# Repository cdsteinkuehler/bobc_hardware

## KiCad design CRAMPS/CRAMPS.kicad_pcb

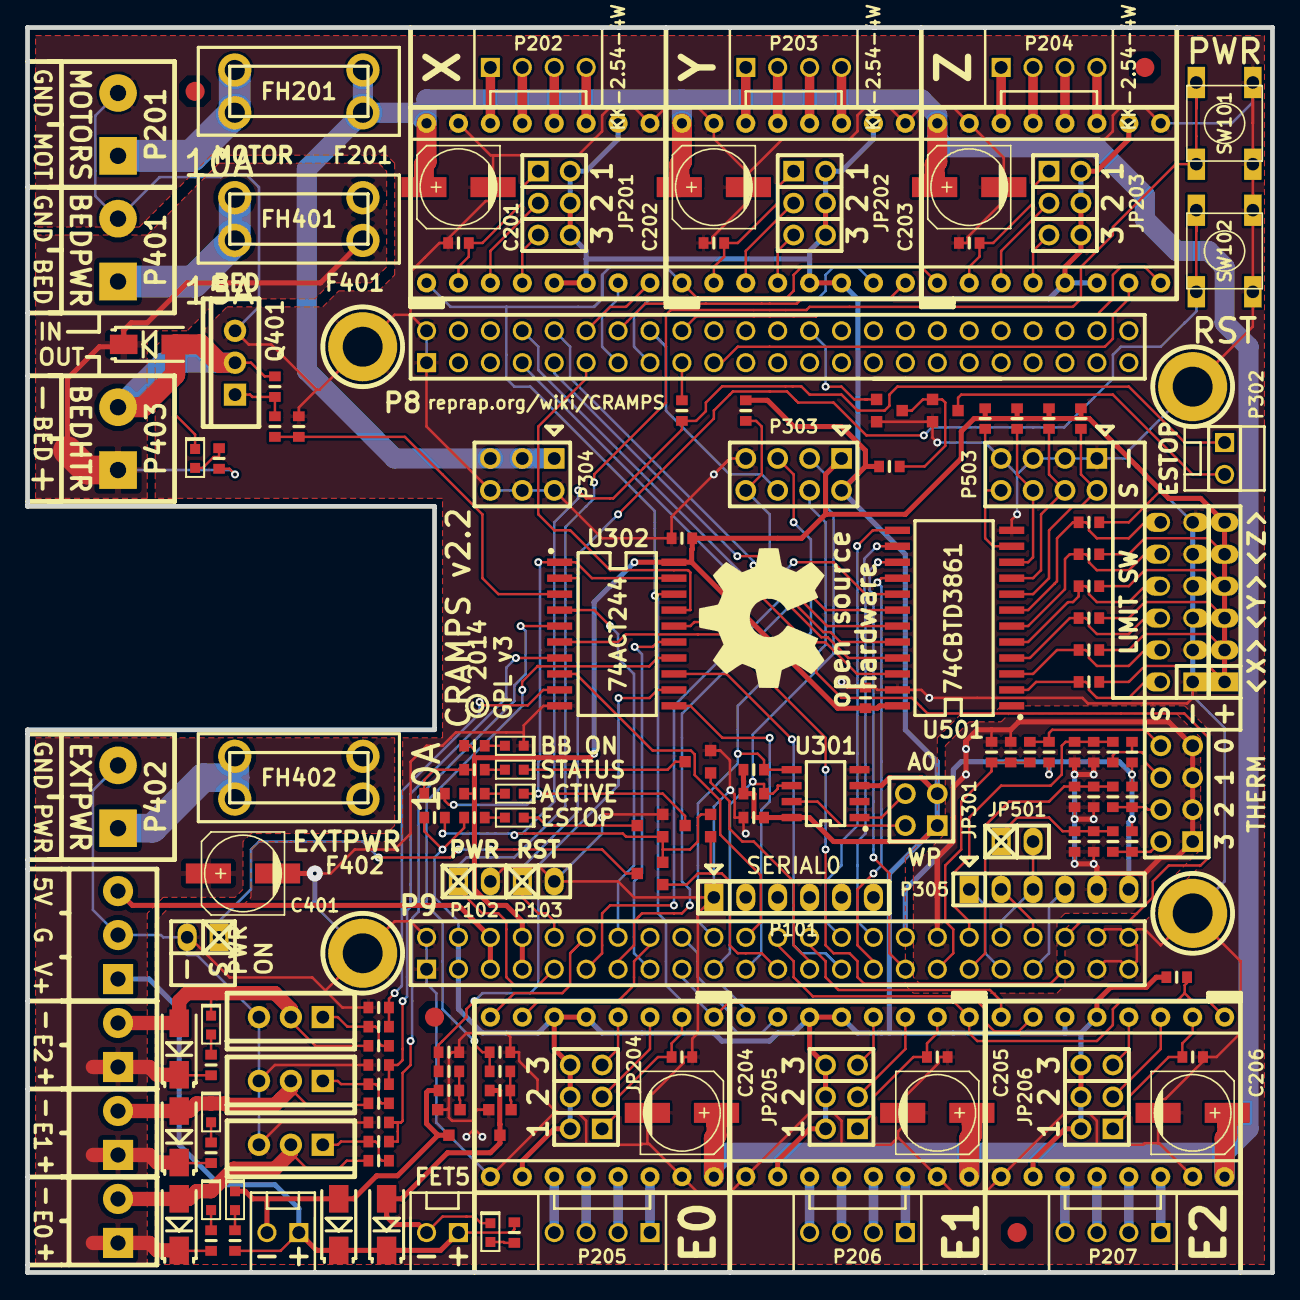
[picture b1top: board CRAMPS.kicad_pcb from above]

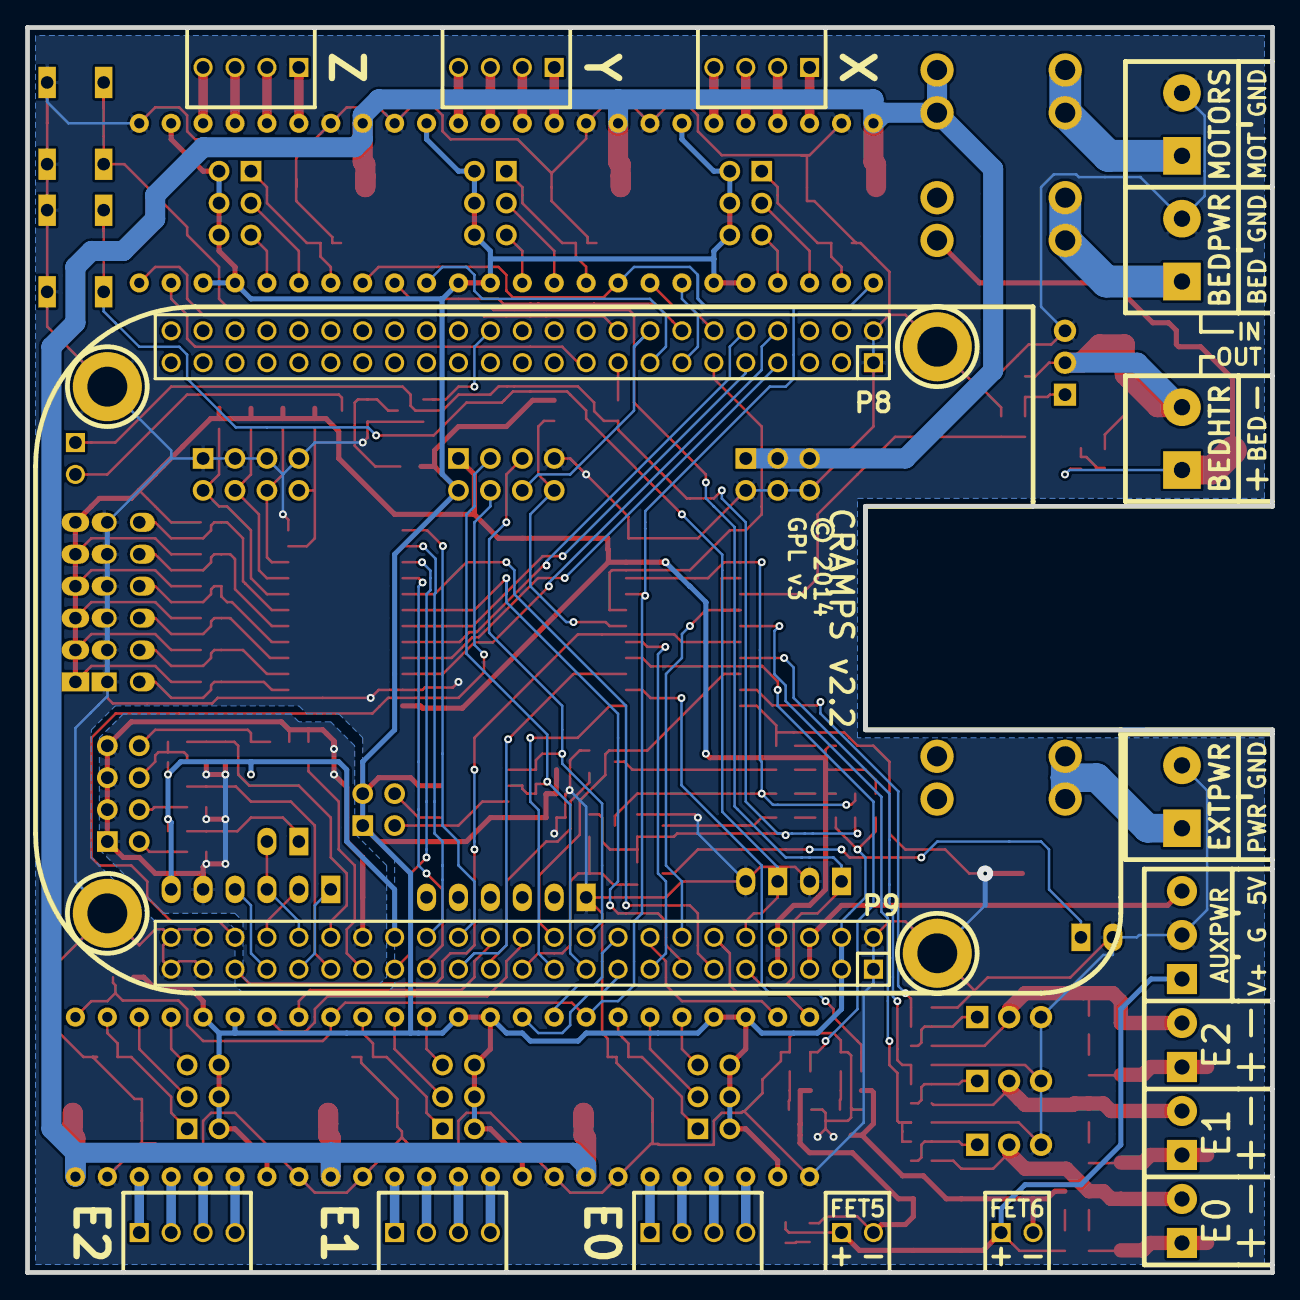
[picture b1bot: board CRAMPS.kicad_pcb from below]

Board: 2 copper layers, 99.1 x 99.1 mm, 192 parts (3 on the bottom side), 155 nets.

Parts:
BB101: BeagleBone Black; BeagleBone-Pins
C201, C202, C203, C204, C205, C206, C401: 100u 35V; c_elec_6.3x7.7
C301, C302, C501, C502, C503, C504, C505: 100n; CAPC1608x55N
C402, C403, C404, C405, C406, C407: None; CAPC1608x55N
C506, C507, C508, C509: 10u; CAPC1608x55N
D401, D402, D403, D404, D405, D406: SS14; DIOM5127X229N
F201, F402: 10A; Fuse-Loose
F401: 15A; Fuse-Loose
FH201, FH401, FH402: FUSE-HOLDER; Keystone-3568
FID1, FID2, FID3, FID4: VAL**; FIDUCIAL-060
JP201, JP202, JP203, JP204, JP205, JP206: HEADER_3X2; pin_strip_3x2
JP301: HEADER_2X2; pin_strip_2x2
JP501: HEADER_2; pin_strip_2
LD101, LD401, LD402, LD403, LD404, LD405, LD406: Yellow; OSRAM-LED-0603
LD102, LD301: Green; OSRAM-LED-0603
LD302: Red; OSRAM-LED-0603
M101: PCB_GREEN_RMC; OSHW_logo_2
M102: LOGO_OSHW; PCB_GREEN_RMC
P8, P9: BB_EXP_CONN; P8P9_PinHeader
P101: SOCKET_6_LONG; pin_strip_6
P102, P103, P301: HEADER_2; pin_strip_2
P201, P401, P402, P403: VAL**; PT_2,5-2-5,0-H
P202, P203, P204, P205, P206, P207: KK-2.54-4W; CONN_KK_2.54_4W
P208, P209, P210, P211: POLOLU_SOCKET; Pololu_Socket
P302, P407, P409: KK-2.54-2W; CONN_KK_2.54_2W
P303, P503, P504: HEADER_4X2; pin_strip_4x2
P304: HEADER_3X2; pin_strip_3x2
P305, P501: HEADER_6; pin_strip_6
P404: VAL**; PT_1,5-3-3,5-H
P405, P406, P408: VAL**; PT_1,5-2-3,5-H
P502: HEADER_6X2; pin_strip_6x2
Q101, Q301, Q302, Q303, Q304, Q305: 2N7002K; SOT23GDS
Q401, Q402, Q403, Q405: IRLB8743PBF; TO-220AB_IRF2804_RMC
Q404, Q406: DMN2075U; SOT23GDS
R101, R102, R303: 330R; RESC1608x55N
R201, R202, R203, R204, R205, R206: 100k; RESC1608x55N
R301, R308, R309, R310, R311, R312, R313, R315, R316, R501, R502, R503, R504, R505, R506, R507, R508, R509, R510: 10k; RESC1608x55N
R302, R402, R404, R406, R408, R410, R412: 2K7; RESC1608x55N
R304, R306, R307, R314, R515, R516, R517, R518: 4k7; RESC1608x55N
R305, R401, R403, R405, R407, R409, R411: 220R; RESC1608x55N
R511, R512, R513, R514: 2K0 1%; RESC1608x55N
S201, S202, S203, S204, S205, S206, S207, S208, S209, S210, S211, S212, S213, S214, S215, S216, S217, S218, S301, S501: SHUNT; Shunt
SW101, SW102: SW_PUSH; SW_6x6_MULTI
U201, U202, U203, U204, U205, U206: Pololu; POLOLU
U301: 24C256; SOIC127P600X175-8AN
U302: 74ACT244; SOIC127P1032X265-20N
U501: 74CBTD3861; SOIC127P1030X265-24N

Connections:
+V_MOTOR: C201.1, C202.1, C203.1, C204.1, C205.1, C206.1, FH201.3, FH201.4, P304.1, P304.3, P304.5, U201.16, U202.16, U203.16, U204.16, U205.16, U206.16
/Emergency Stop/MACHINE_PWRn: LD301.K, Q304.D, R308.2, U302.1, U302.19
/Emergency Stop/PS-On: P301.1, Q302.D
/Inputs/MISO-5V: P503.2, R507.2, U501.8
/Inputs/MOSI-5V: P503.6, R509.2, U501.10
/Inputs/SCK-5V: P503.4, R508.2, U501.9
/Inputs/SPI_CS0-5V: P503.8, R510.2, U501.11
/Mosfet Outputs/Aux_Pwr: D404.K, D406.K, P404.1, P407.1, P409.1, R408.1, R412.1
/Mosfet Outputs/Bed_Fused: D401.K, FH401.3, FH401.4, P403.1, R402.1
/Mosfet Outputs/Bed_HTR: C402.1, D401.A, LD401.K, P403.2, Q401.D
/Mosfet Outputs/Bed_Pwr: FH401.1, FH401.2, P401.1
/Mosfet Outputs/E0_HTR: C403.1, D402.A, LD402.K, P405.2, Q402.D
/Mosfet Outputs/E1_HTR: C404.1, D403.A, LD403.K, P406.2, Q403.D
/Mosfet Outputs/E2_HTR: C405.1, D405.A, LD405.K, P408.2, Q405.D
/Mosfet Outputs/Ext_Fused: C401.1, D402.K, D403.K, D405.K, FH402.3, FH402.4, P405.1, P406.1, P408.1, R404.1, R406.1, R410.1
/Mosfet Outputs/Ext_Pwr: FH402.1, FH402.2
/Mosfet Outputs/P_FET5: C406.1, D404.A, LD404.K, P407.2, Q404.D
/Mosfet Outputs/P_FET6: C407.1, D406.A, LD406.K, P409.2, Q406.D
/Stepper Drivers/E01A: P205.3, U204.12
/Stepper Drivers/E01B: P205.4, U204.11
/Stepper Drivers/E02A: P205.2, U204.13
/Stepper Drivers/E02B: P205.1, U204.14
/Stepper Drivers/E11A: P206.3, U205.12
/Stepper Drivers/E11B: P206.4, U205.11
/Stepper Drivers/E12A: P206.2, U205.13
/Stepper Drivers/E12B: P206.1, U205.14
/Stepper Drivers/E21A: P207.3, U206.12
/Stepper Drivers/E21B: P207.4, U206.11
/Stepper Drivers/E22A: P207.2, U206.13
/Stepper Drivers/E22B: P207.1, U206.14
/Stepper Drivers/MOT_IN: FH201.1, FH201.2, P201.1
/Stepper Drivers/X1A: P202.3, U201.12
/Stepper Drivers/X1B: P202.4, U201.11
/Stepper Drivers/X2A: P202.2, U201.13
/Stepper Drivers/X2B: P202.1, U201.14
/Stepper Drivers/Y1A: P203.3, U202.12
/Stepper Drivers/Y1B: P203.4, U202.11
/Stepper Drivers/Y2A: P203.2, U202.13
/Stepper Drivers/Y2B: P203.1, U202.14
/Stepper Drivers/Z1A: P204.3, U203.12
/Stepper Drivers/Z1B: P204.4, U203.11
/Stepper Drivers/Z2A: P204.2, U203.13
/Stepper Drivers/Z2B: P204.1, U203.14
ADC_GND: C502.2, C503.2, C504.2, C505.2, C506.2, C507.2, C508.2, C509.2, P9.34, P305.5, P504.1, P504.3, P504.5, P504.7
ADC_VDD: P9.32, P305.6, R511.1, R512.1, R513.1, R514.1
AIN0: P9.39, P305.4
AIN1: P9.40, P305.2
AIN2: P9.37, P305.1
AIN3: JP501.2, P9.38, P305.3
AXIS_ENAn: P9.14, U302.2, U302.4
D3.3V: C301.1, JP201.2, JP201.4, JP201.6, JP202.2, JP202.4, JP202.6, JP203.2, JP203.4, JP203.6, JP204.2, JP204.4, JP204.6, JP205.2, JP205.4, JP205.6, JP206.2, JP206.4, JP206.6, JP301.1, JP301.3, P9.3, P9.4, P303.2, R301.1, R304.1, R305.1, R306.1, R307.1, R310.1, R314.1, U201.5, U201.6, U201.10, U202.5, U202.6, U202.10, U203.5, U203.6, U203.10, U204.5, U204.6, U204.10, U205.5, U205.6, U205.10, U206.5, U206.6, U206.10, U301.3, U301.8
DGND: BB101.M1, BB101.M2, BB101.M3, BB101.M4, C201.2, C202.2, C203.2, C204.2, C205.2, C206.2, C301.2, C302.2, C401.2, C501.2, LD102.K, P8.1, P8.2, P9.1, P9.2, P9.43, P9.44, P9.45, P9.46, P101.1, P102.2, P103.2, P201.2, P301.2, P303.7, P304.2, P304.4, P304.6, P401.2, P404.2, P502.1, P502.3, P502.5, P502.7, P502.9, P502.11, P503.1, P503.3, P503.5, P503.7, Q101.S, Q301.S, Q303.S, Q305.S, Q401.S, Q402.S, Q403.S, Q404.S, Q405.S, Q406.S, R201.2, R202.2, R203.2, R204.2, R205.2, R206.2, R309.2, R311.2, R312.2, R313.2, R315.2, R316.2, SW101.2, SW102.2, U201.9, U201.15, U202.9, U202.15, U203.9, U203.15, U204.9, U204.15, U205.9, U205.15, U206.9, U206.15, U301.4, U302.10, U501.12, U501.23
E0_DIR: P9.12, U204.8
E0_EN_BUFn: R314.2, U201.1, U202.1, U203.1, U204.1, U205.1, U206.1, U302.18
E0_STEP: P9.16, U204.7
E1_DIR: P9.18, U205.8
E1_STEP: P9.17, U205.7
E2_DIR: P9.26, U206.8
E2_STEP: P9.24, U206.7
EN_CRAMP3n: P303.8, R310.2, U302.16
ESTOP: P8.17, R302.2
ESTOP_SW: P8.26, Q301.G
FET1: P8.11, U302.17
FET1_BUF: R309.1, R401.2, U302.3
FET2: P9.15, U302.15
FET2_BUF: R311.1, R403.2, U302.5
FET3: P9.27, U302.13
FET3_BUF: R312.1, R405.2, U302.7
FET4: P9.21, U302.11
FET4_BUF: R313.1, R409.2, U302.9
FET5: P9.41, U302.6
FET5_BUF: R316.1, R407.2, U302.14
FET6: P9.22, U302.8
FET6_BUF: R315.1, R411.2, U302.12
LED: P9.25, Q101.G
MACHINE_PWR: P9.23, Q302.G, Q304.G
MISO: P9.29, U501.16
MOSI: P9.30, U501.14
unnamed: C402.2, Q401.G, R401.1
unnamed: C403.2, Q402.G, R403.1
unnamed: C404.2, Q403.G, R405.1
unnamed: C405.2, Q405.G, R409.1
unnamed: C406.2, Q404.G, R407.1
unnamed: C407.2, Q406.G, R411.1
unnamed: JP201.1, R201.1, U201.2
unnamed: JP201.3, U201.3
unnamed: JP201.5, U201.4
unnamed: JP202.1, R202.1, U202.2
unnamed: JP202.3, U202.3
unnamed: JP202.5, U202.4
unnamed: JP203.1, R203.1, U203.2
unnamed: JP203.3, U203.3
unnamed: JP203.5, U203.4
unnamed: JP204.1, R204.1, U204.2
unnamed: JP204.3, U204.3
unnamed: JP204.5, U204.4
unnamed: JP205.1, R205.1, U205.2
unnamed: JP205.3, U205.3
unnamed: JP205.5, U205.4
unnamed: JP206.1, R206.1, U206.2
unnamed: JP206.3, U206.3
unnamed: JP206.5, U206.4
unnamed: JP301.2, U301.7
unnamed: JP301.4, U301.1
unnamed: LD101.A, R101.2
unnamed: LD101.K, Q101.D
unnamed: LD102.A, R102.2
unnamed: LD301.A, R303.2
unnamed: LD302.A, R305.2
unnamed: LD302.K, Q305.D
unnamed: LD401.A, R402.2
unnamed: LD402.A, R404.2
unnamed: LD403.A, R406.2
unnamed: LD404.A, R408.2
unnamed: LD405.A, R410.2
unnamed: LD406.A, R412.2
unnamed: P302.1, Q302.S, Q304.S, Q305.G, R302.1, R304.2
unnamed: P302.2, Q303.D
unnamed: P502.2, R501.2, U501.2
unnamed: P502.4, R502.2, U501.3
unnamed: P502.6, R503.2, U501.4
unnamed: P502.8, R504.2, U501.5
unnamed: P502.10, R505.2, U501.6
unnamed: P502.12, R506.2, U501.7
unnamed: P504.2, R514.2, R518.2
unnamed: P504.4, R513.2, R517.2
unnamed: P504.6, R512.2, R516.2
unnamed: P504.8, R511.2, R515.2
unnamed: Q301.D, Q303.G, R301.2
PWR_BUT: P9.9, P102.1, SW101.1
RESETn: P9.10, P103.1, SW102.1
SCK: P9.31, U501.15
SCL: P9.19, P303.3, R306.2, U301.6
SDA: P9.20, P303.5, R307.2, U301.5
SPI_CS0: P9.28, U501.13
SPI_CS1: P9.42, P303.4
SPI_SPARE: P8.16, P303.6
SYS_5V: C302.1, C501.1, P9.7, P9.8, P303.1, P501.1, P501.2, P501.3, P501.4, P501.5, P501.6, R101.1, R102.1, R303.1, R308.1, R501.1, R502.1, R503.1, R504.1, R505.1, R506.1, R507.1, R508.1, R509.1, R510.1, U302.20, U501.24
THERM0: C502.1, C506.1, P9.33, R515.1
THERM1: C503.1, C507.1, P9.36, R516.1
THERM2: C504.1, C508.1, P9.35, R517.1
THERM3: C505.1, C509.1, JP501.1, R518.1
VDD_5V: P9.5, P9.6, P404.3
X-MAX: P8.7, U501.21
X-MIN: P8.8, U501.22
X_DIR: P8.12, U201.8
X_STEP: P8.13, U201.7
Y-MAX: P8.9, U501.19
Y-MIN: P8.10, U501.20
Y_DIR: P8.14, U202.8
Y_STEP: P8.15, U202.7
Z-MAX: P9.11, U501.17
Z-MIN: P9.13, U501.18
Z_DIR: P8.18, U203.8
Z_STEP: P8.19, U203.7

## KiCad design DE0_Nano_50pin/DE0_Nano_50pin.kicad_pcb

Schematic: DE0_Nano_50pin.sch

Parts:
C1, C2, C3, C4, C7, C8: 100n; CAPC1608x55N; PartNo GRM188R71C104KA01D
GPIO0, GPIO1: CONN_20X2; Pin_Socket_20x2; PartNo SFH11-PBPC-D20-ST-BK
LED1, LED2: Yellow; OSRAM-LED-0805; PartNo LY R976-PS-36
M1, M2, M3, M4: 4-40; MTH_4-40; PartNo Part of PCB
P2, P3, P4: CONN_25X2; pin_strip_25x2; PartNo 30350-6002HB
PTC1, PTC2: 2A; BOURNS-MF-NSMF; PartNo MF-NSMF200-2
R1, R2, R3, R4, R5, R6, R7, R8, R9, R10, R11, R12, R13, R14, R15, R16, R17, R18, R19, R20, R21, R22, R23, R24, R25, R26, R27, R28, R29, R30, R31, R32, R33, R34, R35, R36, R37, R38, R39, R40, R41, R42, R43, R44, R45, R46, R47, R48, R49, R50, R51, R52, R53, R54, R55, R56, R57, R58, R59, R60, R61, R62, R63, R64, R65, R66, R67, R68, R69, R70, R71, R72: 4.7k; RESC1608x55N; PartNo RMCF0603JT4K70
R98, R99: 240R; RESC1608x55N; PartNo RMCF0603JT240R
S1, S2, S3: SHUNT; Shunt; PartNo 382811-8
U1, U2, U3: 74CBT16211; SOP63P1035X279-56N; PartNo SN74CBTD16211ADGGR
W1, W2, W3: HEADER_3; pin_strip_3; PartNo M20-9990345

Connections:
+3.3V: GPIO0.29, GPIO1.29, R98.1, R99.1, W3.3
+5V: C7.1, C8.1, GPIO0.11, GPIO1.11, PTC1.2, PTC2.2, W3.1
/J1-PWR: PTC1.1, W1.1
/J2-PWR: PTC2.1, W2.1
/XIO0: P2.1, R1.2
/XIO1: P2.3, R2.2
/XIO2: P2.5, R3.2
/XIO3: P2.7, R4.2
/XIO4: P2.9, R5.2
/XIO5: P2.11, R6.2
/XIO6: P2.13, R7.2
/XIO7: P2.15, R8.2
/XIO8: P2.17, R9.2
/XIO9: P2.19, R10.2
/XIO10: P2.21, R11.2
/XIO11: P2.23, R12.2
/XIO12: P2.25, R13.2
/XIO13: P2.27, R14.2
/XIO14: P2.29, R15.2
/XIO15: P2.31, R16.2
/XIO16: P2.33, R17.2
/XIO17: P2.35, R18.2
/XIO18: P2.37, R19.2
/XIO19: P2.39, R20.2
/XIO20: P2.41, R21.2
/XIO21: P2.43, R22.2
/XIO22: P2.45, R23.2
/XIO23: P2.47, R24.2
/XIO24: P3.1, R25.2
/XIO25: P3.3, R26.2
/XIO26: P3.5, R27.2
/XIO27: P3.7, R28.2
/XIO28: P3.9, R29.2
/XIO29: P3.11, R30.2
/XIO30: P3.13, R31.2
/XIO31: P3.15, R32.2
/XIO32: P3.17, R33.2
/XIO33: P3.19, R34.2
/XIO34: P3.21, R35.2
/XIO35: P3.23, R36.2
/XIO36: P3.25, R37.2
/XIO37: P3.27, R38.2
/XIO38: P3.29, R39.2
/XIO39: P3.31, R40.2
/XIO40: P3.33, R41.2
/XIO41: P3.35, R42.2
/XIO42: P3.37, R43.2
/XIO43: P3.39, R44.2
/XIO44: P3.41, R45.2
/XIO45: P3.43, R46.2
/XIO46: P3.45, R47.2
/XIO47: P3.47, R48.2
/XIO48: P4.1, R49.2
/XIO49: P4.3, R50.2
/XIO50: P4.5, R51.2
/XIO51: P4.7, R52.2
/XIO52: P4.9, R53.2
/XIO53: P4.11, R54.2
/XIO54: P4.13, R55.2
/XIO55: P4.15, R56.2
/XIO56: P4.17, R57.2
/XIO57: P4.19, R58.2
/XIO58: P4.21, R59.2
/XIO59: P4.23, R60.2
/XIO60: P4.25, R61.2
/XIO61: P4.27, R62.2
/XIO62: P4.29, R63.2
/XIO63: P4.31, R64.2
/XIO64: P4.33, R65.2
/XIO65: P4.35, R66.2
/XIO66: P4.37, R67.2
/XIO67: P4.39, R68.2
/XIO68: P4.41, R69.2
/XIO69: P4.43, R70.2
/XIO70: P4.45, R71.2
/XIO71: P4.47, R72.2
GND: C3.2, C4.2, C7.2, C8.2, GPIO0.12, GPIO0.30, GPIO1.12, GPIO1.30, M1.1, M2.1, M3.1, M4.1, P2.2, P2.4, P2.6, P2.8, P2.10, P2.12, P2.14, P2.16, P2.18, P2.20, P2.22, P2.24, P2.26, P2.28, P2.30, P2.32, P2.34, P2.36, P2.38, P2.40, P2.42, P2.44, P2.46, P2.48, P2.50, P3.2, P3.4, P3.6, P3.8, P3.10, P3.12, P3.14, P3.16, P3.18, P3.20, P3.22, P3.24, P3.26, P3.28, P3.30, P3.32, P3.34, P3.36, P3.38, P3.40, P3.42, P3.44, P3.46, P3.48, P3.50, P4.2, P4.4, P4.6, P4.8, P4.10, P4.12, P4.14, P4.16, P4.18, P4.20, P4.22, P4.24, P4.26, P4.28, P4.30, P4.32, P4.34, P4.36, P4.38, P4.40, P4.42, P4.44, P4.46, P4.48, P4.50, W2.3; also elsewhere on the board
unnamed: P4.49, R49.1, R50.1, R51.1, R52.1, R53.1, R54.1, R55.1, R56.1, R57.1, R58.1, R59.1, R60.1, R61.1, R62.1, R63.1, R64.1, R65.1, R66.1, R67.1, R68.1, R69.1, R70.1, R71.1, R72.1
unnamed: LED2.A, R99.2
unnamed: LED1.A, R98.2
unnamed: P2.49, R1.1, R2.1, R3.1, R4.1, R5.1, R6.1, R7.1, R8.1, R9.1, R10.1, R11.1, R12.1, R13.1, R14.1, R15.1, R16.1, R17.1, R18.1, R19.1, R20.1, R21.1, R22.1, R23.1, R24.1
unnamed: C3.1, C4.1, W2.2
unnamed: C1.2, C2.2, W1.3
unnamed: C1.1, C2.1, W1.2
unnamed: P3.49, R25.1, R26.1, R27.1, R28.1, R29.1, R30.1, R31.1, R32.1, R33.1, R34.1, R35.1, R36.1, R37.1, R38.1, R39.1, R40.1, R41.1, R42.1, R43.1, R44.1, R45.1, R46.1, R47.1, R48.1

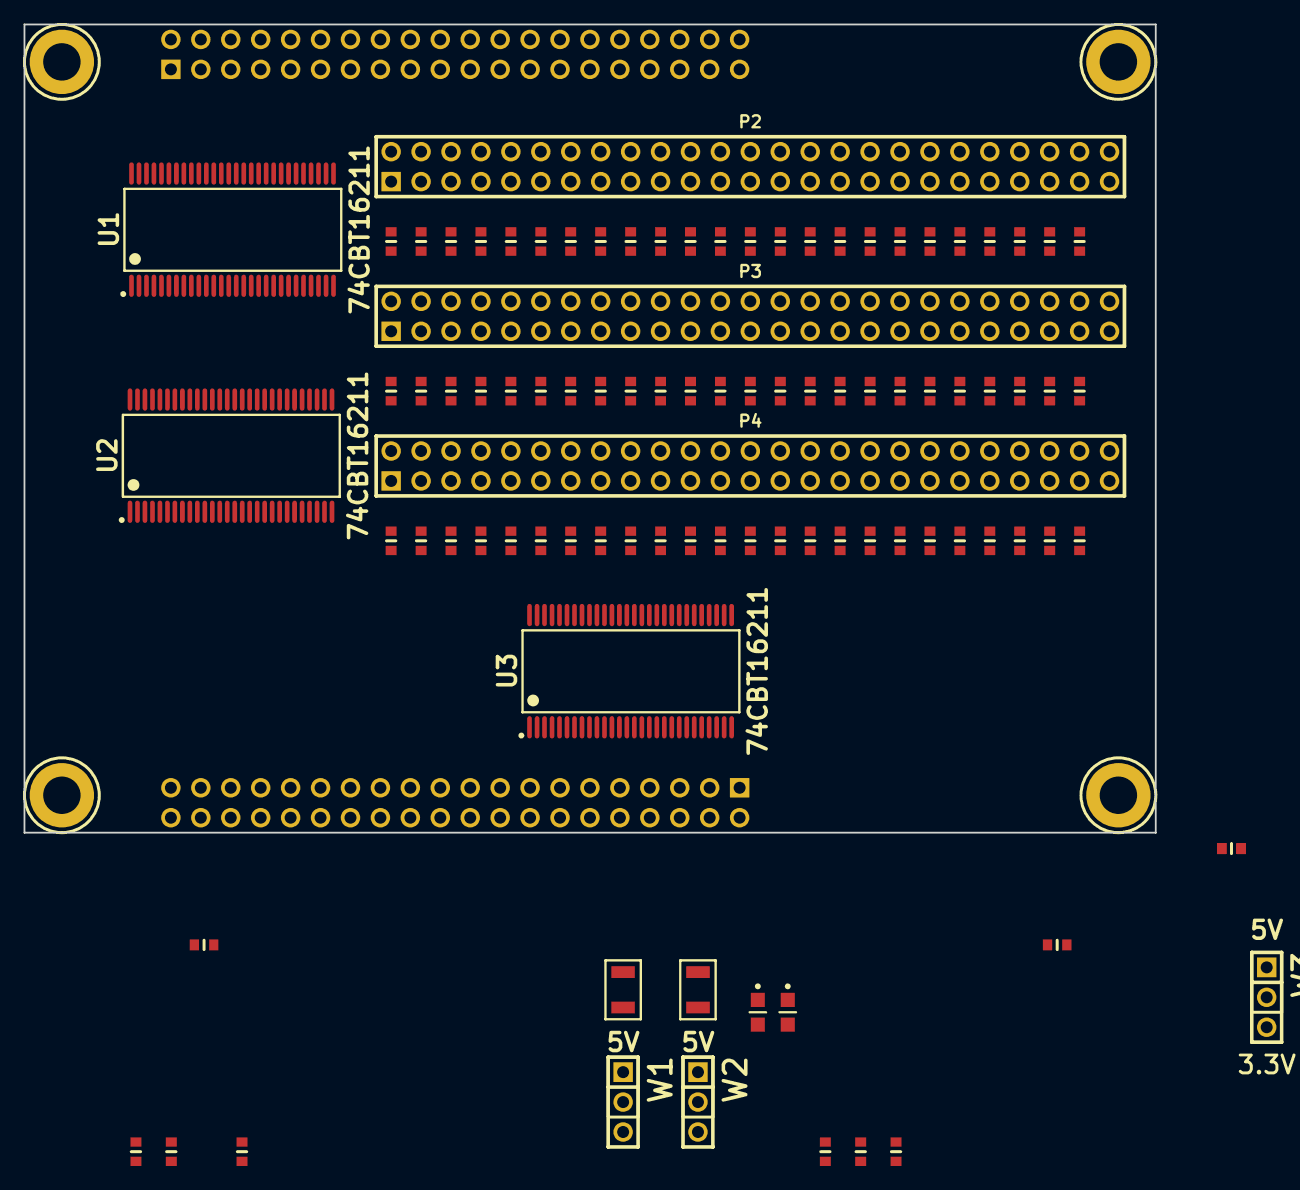
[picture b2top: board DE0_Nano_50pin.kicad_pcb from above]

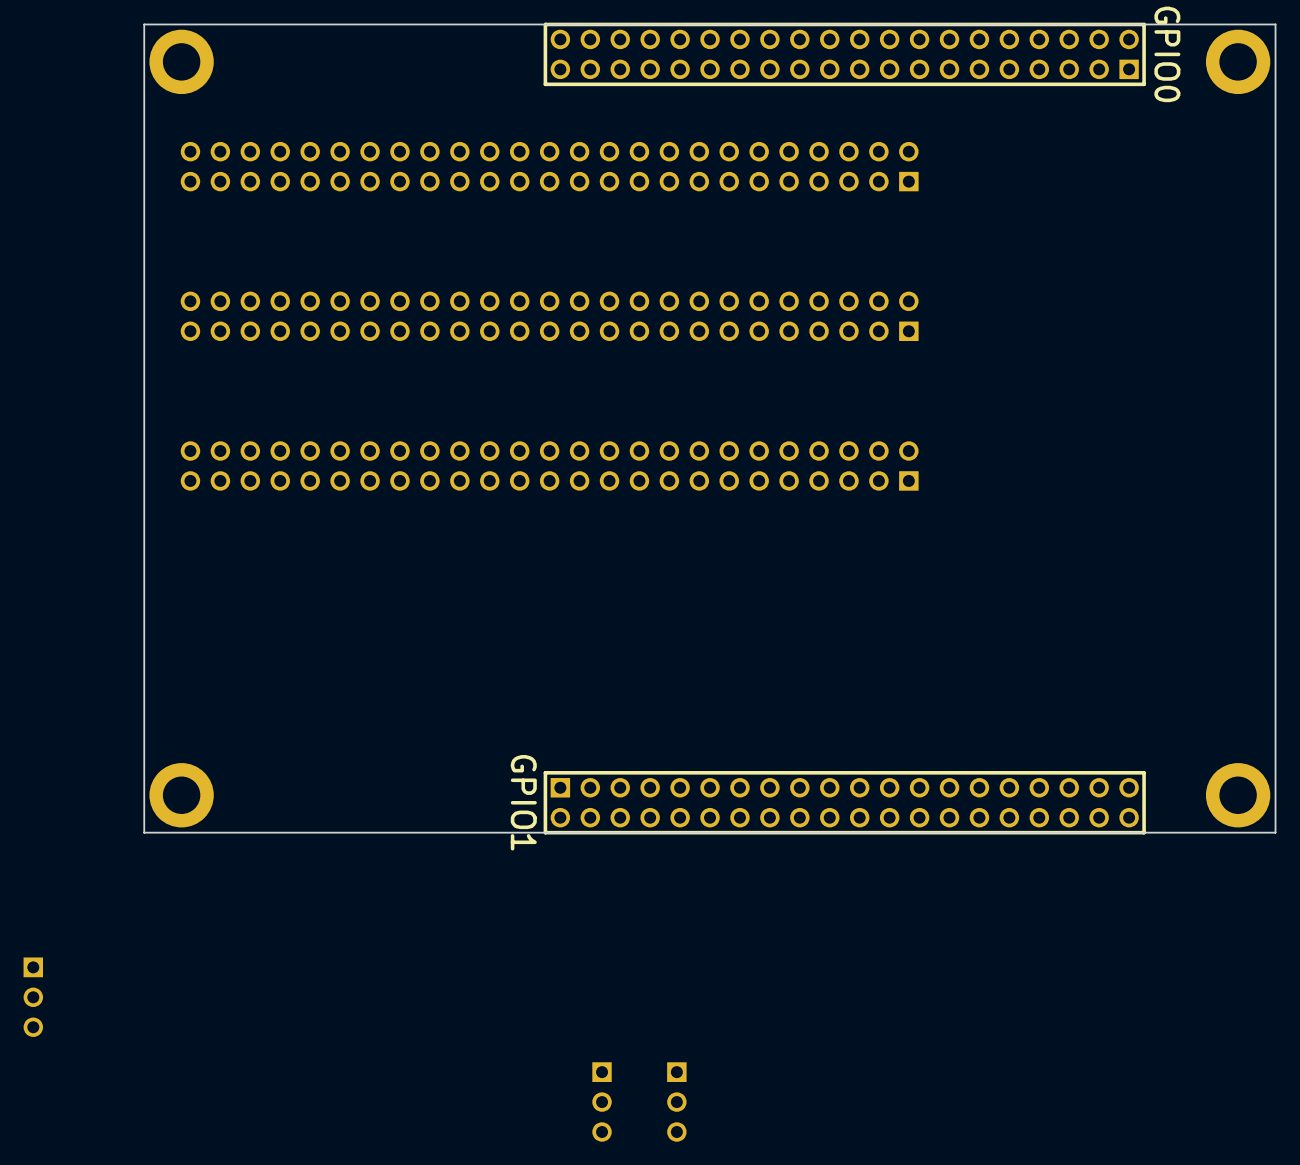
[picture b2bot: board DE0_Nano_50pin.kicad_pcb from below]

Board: 2 copper layers, 96.0 x 68.6 mm, 104 parts (2 on the bottom side), 86 nets, no tracks yet.

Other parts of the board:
C5, C6: 100n; CAPC1608x55N

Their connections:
/VPU: C5.1, C6.1
GND: C5.2, C6.2; also elsewhere on the board

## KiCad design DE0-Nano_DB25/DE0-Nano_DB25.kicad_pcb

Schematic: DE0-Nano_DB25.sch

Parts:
C1, C2, C3, C4, C5, C6, C7, C8: 100n; CAPC1608x55N; PartNo GRM188R71C104KA01D
LED1, LED2: Yellow; OSRAM-LED-0805; PartNo LY R976-PS-36
M1, M2: 4-40; MTH_4-40; PartNo Part of PCB
P1: CONN_20X2; Pin_Socket_20x2; PartNo SFH11-PBPC-D20-ST-BK
P2, P3: DB25; AMP-5747846; PartNo 5747846-4
PTC1, PTC2: 2A; BOURNS-MF-NSMF; PartNo MF-NSMF200-2
R1, R2, R3, R4, R5, R6, R7, R8, R9, R10, R11, R12, R13, R14, R15, R16, R17, R18, R19, R20, R21, R22, R23, R24, R25, R26, R27, R28, R29, R30, R31, R32, R33, R34: 3.3k; RESC1608x55N; PartNo RMCF0603JT3K30
R35, R36: 240R; RESC1608x55N; PartNo RMCF0603JT240R
S1, S2, S3: SHUNT; Shunt; PartNo 382811-8
U1, U2, U3, U4: 74CBTLV3861; SOIC127P1030X265-24N; PartNo SN74CBTD3861DW
W1, W2, W3: HEADER_3; pin_strip_3; PartNo M20-9990345

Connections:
+3.3V: P1.29, R35.1, R36.1, W3.3
+5V: C7.1, C8.1, P1.11, PTC1.2, PTC2.2, U1.24 (VCC), U2.24 (VCC), U3.24 (VCC), U4.24 (VCC), W3.1
/J1-0: P2.1, R1.2, U2.10 (A9)
/J1-1: P2.14, R2.2, U2.9 (A8)
/J1-2: P2.2, R3.2, U2.8 (A7)
/J1-3: P2.15, R4.2, U2.7 (A6)
/J1-4: P2.3, R5.2, U2.6 (A5)
/J1-5: P2.16, R6.2, U2.5 (A4)
/J1-6: P2.4, R7.2, U2.4 (A3)
/J1-7: P2.17, R8.2, U2.3 (A2)
/J1-8: P2.5, R9.2, U2.2 (A1)
/J1-9: P2.6, R10.2, U1.11 (A10)
/J1-10: P2.7, R11.2, U1.10 (A9)
/J1-11: P2.8, R12.2, U1.9 (A8)
/J1-12: P2.9, R13.2, U1.8 (A7)
/J1-13: P2.10, R14.2, U1.7 (A6)
/J1-14: P2.11, R15.2, U1.6 (A5)
/J1-15: P2.12, R16.2, U1.5 (A4)
/J1-16: P2.13, R17.2, U1.4 (A3)
/J1-PWR: PTC1.1, W1.1
/J1B0: P1.19, U2.14 (B9)
/J1B1: P1.20, U2.15 (B8)
/J1B2: P1.17, U2.16 (B7)
/J1B3: P1.18, U2.17 (B6)
/J1B4: P1.15, U2.18 (B5)
/J1B5: P1.16, U2.19 (B4)
/J1B6: P1.13, U2.20 (B3)
/J1B7: P1.14, U2.21 (B2)
/J1B8: P1.9, U2.22 (B1)
/J1B9: P1.10, U1.13 (B10)
/J1B10: P1.7, U1.14 (B9)
/J1B11: P1.8, U1.15 (B8)
/J1B12: P1.5, U1.16 (B7)
/J1B13: P1.6, U1.17 (B6)
/J1B14: P1.3, U1.18 (B5)
/J1B15: P1.4, U1.19 (B4)
/J1B16: P1.1, U1.20 (B3)
/J2-0: P3.1, R18.2, U4.10 (A9)
/J2-1: P3.14, R19.2, U4.9 (A8)
/J2-2: P3.2, R20.2, U4.8 (A7)
/J2-3: P3.15, R21.2, U4.7 (A6)
/J2-4: P3.3, R22.2, U4.6 (A5)
/J2-5: P3.16, R23.2, U4.5 (A4)
/J2-6: P3.4, R24.2, U4.4 (A3)
/J2-7: P3.17, R25.2, U4.3 (A2)
/J2-8: P3.5, R26.2, U4.2 (A1)
/J2-9: P3.6, R27.2, U3.11 (A10)
/J2-10: P3.7, R28.2, U3.10 (A9)
/J2-11: P3.8, R29.2, U3.9 (A8)
/J2-12: P3.9, R30.2, U3.8 (A7)
/J2-13: P3.10, R31.2, U3.7 (A6)
/J2-14: P3.11, R32.2, U3.6 (A5)
/J2-15: P3.12, R33.2, U3.5 (A4)
/J2-16: P3.13, R34.2, U3.4 (A3)
/J2-PWR: PTC2.1, W2.1
/J2B0: P1.39, U4.14 (B9)
/J2B1: P1.40, U4.15 (B8)
/J2B2: P1.37, U4.16 (B7)
/J2B3: P1.38, U4.17 (B6)
/J2B4: P1.35, U4.18 (B5)
/J2B5: P1.36, U4.19 (B4)
/J2B6: P1.33, U4.20 (B3)
/J2B7: P1.34, U4.21 (B2)
/J2B8: P1.31, U4.22 (B1)
/J2B9: P1.32, U3.13 (B10)
/J2B10: P1.27, U3.14 (B9)
/J2B11: P1.28, U3.15 (B8)
/J2B12: P1.25, U3.16 (B7)
/J2B13: P1.26, U3.17 (B6)
/J2B14: P1.23, U3.18 (B5)
/J2B15: P1.24, U3.19 (B4)
/J2B16: P1.21, U3.20 (B3)
/LED0: LED1.K, P1.2
/LED1: LED2.K, P1.22
/VPU: C5.1, C6.1, R1.1, R2.1, R3.1, R4.1, R5.1, R6.1, R7.1, R8.1, R9.1, R10.1, R11.1, R12.1, R13.1, R14.1, R15.1, R16.1, R17.1, R18.1, R19.1, R20.1, R21.1, R22.1, R23.1, R24.1, R25.1, R26.1, R27.1, R28.1, R29.1, R30.1, R31.1, R32.1, R33.1, R34.1, W3.2
GND: C1.2, C2.2, C3.2, C4.2, C5.2, C6.2, C7.2, C8.2, M1.1, M2.1, P1.12, P1.30, P2.18, P2.19, P2.20, P2.21, P3.18, P3.19, P3.20, P3.21, U1.12 (GND), U1.23 (~OE), U2.12 (GND), U2.23 (~OE), U3.12 (GND), U3.23 (~OE), U4.12 (GND), U4.23 (~OE), W1.3, W2.3
unnamed: C3.1, C4.1, P3.22, P3.23, P3.24, P3.25, W2.2
unnamed: LED1.A, R35.2
unnamed: LED2.A, R36.2
unnamed: C1.1, C2.1, P2.22, P2.23, P2.24, P2.25, W1.2

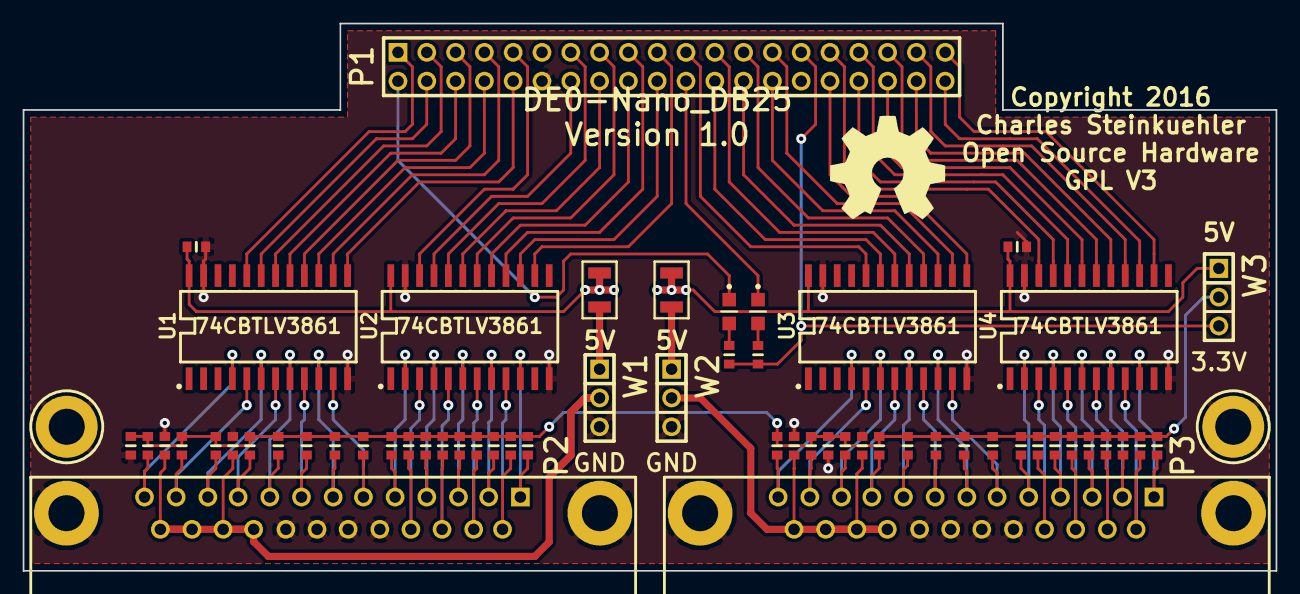
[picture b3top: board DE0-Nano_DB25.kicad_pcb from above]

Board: 2 copper layers, 110.5 x 48.3 mm, 63 parts (0 on the bottom side), 80 nets.

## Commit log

2016-04-16 DE0-Nano_DB25: New Project
    Initial schematic for the DE0-Nano_DB25 project, which aims to connect
    the DE0-Nano development board to standard Mesanet DB25 daughtercards
    by replicating the I/O and connector section of a 5i25.
2016-04-17 DE0-Nano_DB25
    Initial PCB placed and routed
    Ready for final cleanup and gerber file generation
2016-04-17 DE0-Nano_DB25: Initial Version
    PCB complete and gerbers generated.
2016-08-09 DE0_Nano_50pin initial version (WIP)
    Adapter board to use the DE0_Nano_SoC with Mesanet.com 50-pin
    Anything I/O daughter cards. This version just has a basic PCB
    outline and the 50-pin connectors for review of the placement and
    mechanical issues.
2016-10-19 DE0-Nano_DB25: Add BOM spreadsheet
    Add BOM spreadsheet with manufacturer part numbers
2016-10-19 DE0-Nano_DB25: Update value field for bus level translators
    Change the value field for the bus level translators from the incorrect
    LVT family (inherited from the standard KiCAD library) to the correct
    CBTD family.
2017-06-12 Update level translators
    Switch to 74CBTD16211 level transators in SOP package
2017-09-12 DE0_Nano_50pin/DE0_Nano_50pin.sch: connect level pins to 50pin
2019-04-12 Add DE0-Nano_DB25 assembly drawing
2019-04-21 Migrate CRAMPS to Kicad v5
2019-04-21 Added CRAMPS KiCad 5 readme file
2019-04-21 CRAMPS Kicadv5 update RMC lib and disable opendous library to silence schematic load errors

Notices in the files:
CRAMPS/CRAMPS.kicad_pcb:
Copyright 2014 GPL v3
© 2014
GPL v3
DE0-Nano_DB25/DE0-Nano_DB25.kicad_pcb:
Copyright 2016
DE0-Nano_DB25/DE0-Nano_DB25.sch:
Copyright 2016 GPL v3
